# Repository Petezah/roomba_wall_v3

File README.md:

# roomba_wall_v3

An AVR device, based on ATTiny45, to transmit a virtual wall signal for an iRobot Roomba

## Folder layout

* /firmware
  * Source for the ATTiny45 firmware
* /hardware
  * Files describing the board layout, etc
  * Use [KiCad](https://www.kicad.org/) to view/edit

## Building

### Prerequisites for "happy path":

* An AVR programmer
  * If you don't have one, you can build mine: https://oshpark.com/shared_projects/O24XLDbo
  * Though, this is a chicken-egg problem.  You can always program the programmer with an Arduino or a Raspberry Pi.
* AVR-GCC installed
  *  Easiest way to get this is 'sudo apt-get install arduino'
* A 6-position, dual-row IDC cable
* A 6-position, dual-row, male header to either:
  * Solder onto your board for programming, or
  * Plug into the IDC cable and "wedge" it into the ISP header during programming (recommended, and is what I do)

### Steps

#### hardware

* Order a board based on the files in https://github.com/Petezah/roomba_wall_v3/tree/master/hardware
  * Alternately, order one directly from OSH Park here: https://oshpark.com/shared_projects/i2FdXslA
* Purchase parts from [Mouser electronics](http://mouser.com) using the current BOM
  * Use the ones with "mouser" in their filenames
* Assemble the board--part references are all marked on the silkscreen
  * NB: The ISP header should not be soldered to the board--merely insert the header pins into the IDC cable and wedge the pins into the vias during programming

#### firmware

There are two methods to wire the board for programming:

* *Recommended way*:
  *  Order my AVR programmer board here: https://oshpark.com/shared_projects/O24XLDbo
  *  Assemble, and use an IDC cable as described above

* Alternate way:
  *  Order my Raspberry Pi ISP board here: https://oshpark.com/shared_projects/iYtnPahC
  * Or hook up the ISP pins on the assembled board to your Raspberry PI as follows:
    * ISP Pin 1 --> Raspberry Pi Pin 21 (MISO)
    * ISP Pin 2 --> Raspberry Pi Pin 17 (3.3V)
    * ISP Pin 3 --> Raspberry Pi Pin 23 (SCK)
    * ISP Pin 4 --> Raspberry Pi Pin 19 (MOSI)
    * ISP Pin 5 --> Raspberry Pi Pin 15 (GPIO22)
    * ISP Pin 6 --> Raspberry Pi Pin 25 (GND)

Once wiring is accomplished:
* Execute the following on the Raspberry Pi command line
  * cd firmware
  * make fuse
  * make install

## Operating

There are a few different ways to operate this device.

### Default (easy) timed mode

When the device is off (sleeping), simply press and release the button once.  The device will respond by turning the indicator LED on for one second and then turning it off.  After this, the device will operate for 3 hours and then go to sleep again.

### Custom timed mode

When the device is off (sleeping), hold down the button.  The device will blink briefly, once every half second.  Every blink corresponds to 15 minutes of operation.  For example, if you want the device to operate for 30 minutes, you will wait for 2 blinks; or, if you want the device to operate for 1 hour and 15 minutes, you will wait for 5 blinks.  Once you reach the desired count, release the button.  The device will then wait, and will then blink the LED indicator the number of times it has counted for the running time.  After this, the device will run for the set time, and then will go to sleep.

### Turning off the device (putting it to sleep manually)

When the device is operating, hold down the button for two seconds.  The device will blink 3 times rapidly.  Now release the button, and the device will blink 2 times rapidly, and will then go to sleep.

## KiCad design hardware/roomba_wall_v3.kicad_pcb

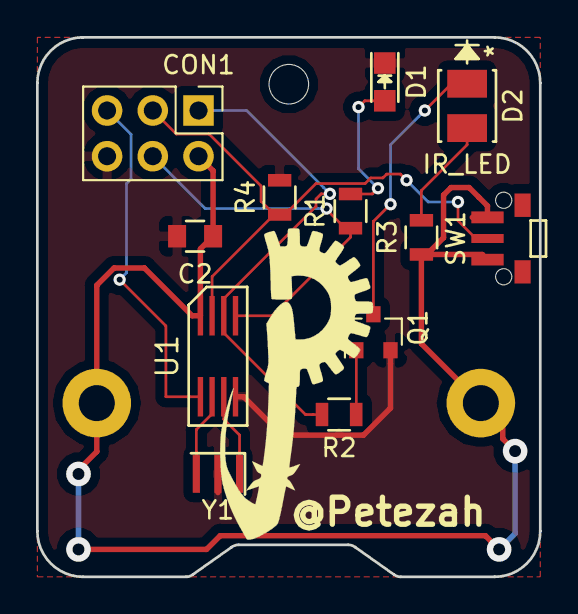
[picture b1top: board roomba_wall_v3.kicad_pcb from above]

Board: 2 copper layers, 27.9 x 30.0 mm, 13 parts (1 on the bottom side), 12 nets.

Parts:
BT1: Battery_Cell; CR2032-THRU
C2: 10uF; C_0805
CON1: AVR-ISP-6; Pin_Header_Straight_2x03_Pitch2.54mm
D1: LED; LED_0805
D2: IR_LED; VSMB3940X01-GS08
Q1: Q_NPN_BEC; SOT-23
R1, R2: 560; R_0805
R3: 51; R_0805
R4: 10k; R_0805
SW1: Button; e-switch-TL-3340-AF160QG
U1: ATTINY45-20SU; ATtiny45V-10XU-TSSOP-8
Y1: 8Mhz; Resonator_SMD_muRata_CSTCE_G-3pin_3.0x0.7mm

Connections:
+3V3: BT1.1, C2.1, CON1.2, R3.1, SW1.1, U1.8
/MISO/IR: CON1.1, R2.1, U1.6
/MOSI/INDICATOR: CON1.4, R1.1, U1.5
/RST: CON1.5, U1.1
/SCK/BUTTON: CON1.3, R4.1, SW1.2, U1.7
GND: BT1.2, C2.2, CON1.6, D1.1, Q1.2, R4.2, U1.4, Y1.2
unnamed: D1.2, R1.2
unnamed: D2.1, Q1.3
unnamed: D2.2, R3.2
unnamed: Q1.1, R2.2
unnamed: U1.2, Y1.1
unnamed: U1.3, Y1.3

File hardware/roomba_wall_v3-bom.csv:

Reference, Value, Footprint, Datasheet, MPN
"U1","ATTINY45-20SU","lib_fp:ATtiny45V-10XU-TSSOP-8","","ATTINY45-20XU"
"Y1","8Mhz","lib_fp:Resonator_SMD_muRata_CSTCE_G-3pin_3.0x0.7mm","","CSTNE8M00G55A000R0"
"R1","560","lib_fp:R_0805","","ERJ-6ENF5600V"
"R2","560","lib_fp:R_0805","","ERJ-6ENF5600V"
"R3","51","lib_fp:R_0805","","ERJ-6ENF51R0V"
"D1","LED","lib_fp:LED_0805","","IN-S85ATR"
"D2","IR_LED","kicad-libs:VSMB3940X01-GS08","","VSMB3940X01-GS08"
"CON1","AVR-ISP-6","lib_fp:Pin_Header_Straight_2x03_Pitch2.54mm",""
"C2","10uF","lib_fp:C_0805","","885012107004"
"Q1","Q_NPN_BEC","lib_fp:SOT-23","","SMMBT2222ALT3G"
"BT1","Battery_Cell","lib_fp:CR2032-THRU","","12BH003-GR"
"SW1","Button","lib_fp:e-switch-TL-3340-AF160QG","","TL3340AF160QG"
"R4","10k","lib_fp:R_0805","","ERJ-6ENF1002V"

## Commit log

2018-02-24 Allow the wake time to be set via a button hold
2018-02-25 Rename target to v3
2018-02-25 Start v3 PCB project
2018-02-25 Start v3 hardware from the Christmas tree barrier point
2018-02-28 Reorg/rename a bit
2018-02-28 Schematic for v3 Added a user button mostly Changed to a switch and a battery, like v2 (from Christmas Barrier)
2018-02-28 Reorganize and sanitize libraries again
2018-02-28 Progress on annotating and reassigning footprints I want to use 0805, since they seem the easiest and cheapest to source
2018-03-03 Updated footprint associations, etc for v3
2018-03-03 Fix fp archive pointers
2018-03-03 Fix all ERC errors
2018-03-21 Placed and routed new PCB layout
2018-03-21 Refill zones
2018-04-15 Added a mounting hole for hanging and finalized layout for rev A Also exported gerbers
2018-04-16 Update README and footprint lib archive
2018-04-16 Schematic plot
2018-04-16 Exported basic BOM
2018-05-06 Tweak delays * 15 minutes runtime per LED blink * 30000 delay per IR TX
2018-05-06 Some renaming and reformatting
2018-08-03 Working on rev B
2018-08-05 Add simple travis script
2018-08-05 Fix directory for make ci command
2018-08-05 Finished rev-b layout Updated gerbers Updated BOM Updated footprint archive Updated PDF schematic plot
2018-08-05 Add deploy script
2018-08-05 Release on tags
2018-08-06 Fix deploy script
2018-08-06 Deploy master and develop
2018-08-06 Remove travis; not that happy with it
2018-08-20 Clean up makefile
2018-08-20 Fix mistake
2018-08-20 New behavior: * 1 quick press -> on for default period (3 hours) * hold down -> set for 15 minutes per blink * from running, hold down for 2 seconds -> turn off
    long LED blink will indicate #1
    quick LED blinks will indicate #2, and amount of time running
    3 quick LED blinks will indicate #3, that device will turn off
2018-08-22 Fix bug in shutdown code If the user releases the button in shutdown mode before shutdown has occurred, the state should just revert to the running state. This will allow the button counters to retur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
2018-08-22 Updated README and image
2018-11-05 Add MPN to BOM
2019-01-21 Adjust fuse settings
2019-02-04 Upgraded to Kicad 5
2019-05-02 Generate interactive BOM Move CSV BOM into folder
2019-05-02 Update format
2019-05-13 Updated gerbers
2019-05-13 Make shutdown more error-proof
2019-05-13 Put operating instructions into the readme
2021-04-04 Add a watchdog timer and change default time
    Add a watchdog timer to reset the device if it crashes.
    Change the "default" run time to 2 hours instead of 3
2022-12-20 README: mention KiCad

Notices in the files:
hardware/roomba_wall_v3.kicad_pcb:
(C) 2018 Peter Dunshee
(C) Copyright 2018 Peter Dunshee
parts and their libraries:
Copyright 2016 Accelerated Designs. All rights reserved.
